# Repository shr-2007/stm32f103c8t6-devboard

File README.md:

# Canal Star Tech - STM32F103C8T6 Development Board

A custom STM32F103C8T6 development-board design created in KiCad as a hands-on electronics and PCB-design learning project.

> **Project status:** Designed in KiCad; not yet fabricated or hardware-tested.
> This repository documents the hardware design and its manufacturing outputs. It does not currently include firmware.

## Overview

The board is built around the **STM32F103C8T6** microcontroller and is intended as a compact platform for learning STM32 development, embedded hardware, and PCB design.

### Intended board features

- STM32F103C8T6 microcontroller
- 16 MHz external high-speed crystal (verify against the final schematic before fabrication)
- USB connectivity
- SWD programming/debug header
- UART header
- I²C header
- 3.3 V regulation using an AMS1117-3.3 regulator
- BOOT0 and reset access
- Front- and back-copper routing on a two-layer PCB
- GND copper zone on the back copper layer

**Important:** Confirm all component values, connector pinouts, USB circuitry, power-input limits, and regulator requirements against the committed schematic and datasheets. The feature list above reflects the current design notes and should be updated if the final schematic differs.

## Repository layout

```text
.
├── Hardware/
│   ├── KiCad/          # Native KiCad project files and required local libraries
│   ├── Gerber/         # Gerber artwork, drill files, and job file
│   └── PDF/            # Schematic PDF and other exported drawings
├── Images/             # PCB renders, layout screenshots, schematic preview
├── Documentation/
│   ├── BOM.csv         # Bill of materials template
│   └── Design_Notes.md # Design decisions and verification notes
├── LICENSE
├── README.md
└── .gitignore
```

## Design files

| Artifact | Location |
|---|---|
| KiCad schematic | `Hardware/KiCad/` |
| KiCad PCB layout | `Hardware/KiCad/` |
| Schematic PDF | `Hardware/PDF/` |
| Gerber files | `Hardware/Gerber/` |
| Excellon drill files (`.drl`) | `Hardware/Gerber/` |
| 3D render and board images | `Images/` |
| Bill of materials | `Documentation/BOM.csv` |

## Interfaces

The design currently provides headers or connections intended for:

| Interface | Purpose |
|---|---|
| USB | USB connectivity |
| SWD | Programming and debugging |
| UART | Serial communication |
| I²C | External peripherals and sensors |
| BOOT0 | Boot-mode selection |
| NRST | Reset |

Refer to the schematic and PCB silkscreen for the exact pin assignments. Do not infer pinouts from connector position alone.

## Design and verification notes

The board has been laid out as a two-layer PCB. The back copper layer contains a GND copper zone. Ground-net highlighting was used during design review to check the intended ground network.

Gerber and drill outputs were generated and opened in KiCad Gerber Viewer for visual inspection.

Before fabrication, perform and record a final review of:

- Schematic-to-PCB consistency (Update PCB from Schematic / comparison)
- Final DRC results, including any intentional exceptions
- Unconnected items
- USB schematic and routing against the STM32F103C8T6 datasheet and USB design guidance
- Crystal placement, load capacitors, and oscillator routing
- BOOT0 and NRST circuitry
- SWD header pinout
- Regulator input/output capacitors, dissipation, and input-voltage limits
- Drill sizes, plated/non-plated hole assignments, and mounting-hole dimensions
- Solder-mask and silkscreen clearances
- Manufacturer capability limits for trace width, spacing, annular ring, and drill size

A clean DRC report is useful, but it does not prove that the circuit is electrically correct or that the board has been hardware-tested.

## Getting started

1. Install KiCad (use a version compatible with the project files).
2. Clone this repository:
   ```bash
   git clone https://github.com/shr-2007/stm32f103c8t6-devboard.git
   cd stm32f103c8t6-devboard
   ```
3. Open the `.kicad_pro` file from `Hardware/KiCad/` in KiCad.
4. Check that any project-specific symbol and footprint libraries resolve correctly.
5. Review the schematic and PCB before making changes.

## Manufacturing outputs

The `Hardware/Gerber/` folder is intended to contain:

- Front and back copper Gerbers
- Front and back solder-mask Gerbers
- Front and back silkscreen Gerbers, if used
- Board outline (`Edge.Cuts`)
- PTH and NPTH Excellon drill files
- Gerber job file

Before sending files to a manufacturer, compress only the required fabrication outputs into a separate ZIP and inspect that ZIP with the manufacturer's Gerber viewer or upload preview. Do not include the native KiCad files in the fabrication ZIP unless the manufacturer specifically requests them.

## License

The hardware design is intended to be released under **CERN Open Hardware Licence Version 2 — Strongly Reciprocal (CERN-OHL-S-2.0)**. See [`LICENSE`](LICENSE).

If you add software, firmware, documentation, images, or third-party assets later, review whether separate licenses or attribution notices are appropriate. Do not assume the hardware license automatically covers third-party assets.

## Credits

Designed as an independent electronics and PCB-design
learning project.

Board branding: Canal Star Tech (fictional project identity).
Designed by: shr-2007.

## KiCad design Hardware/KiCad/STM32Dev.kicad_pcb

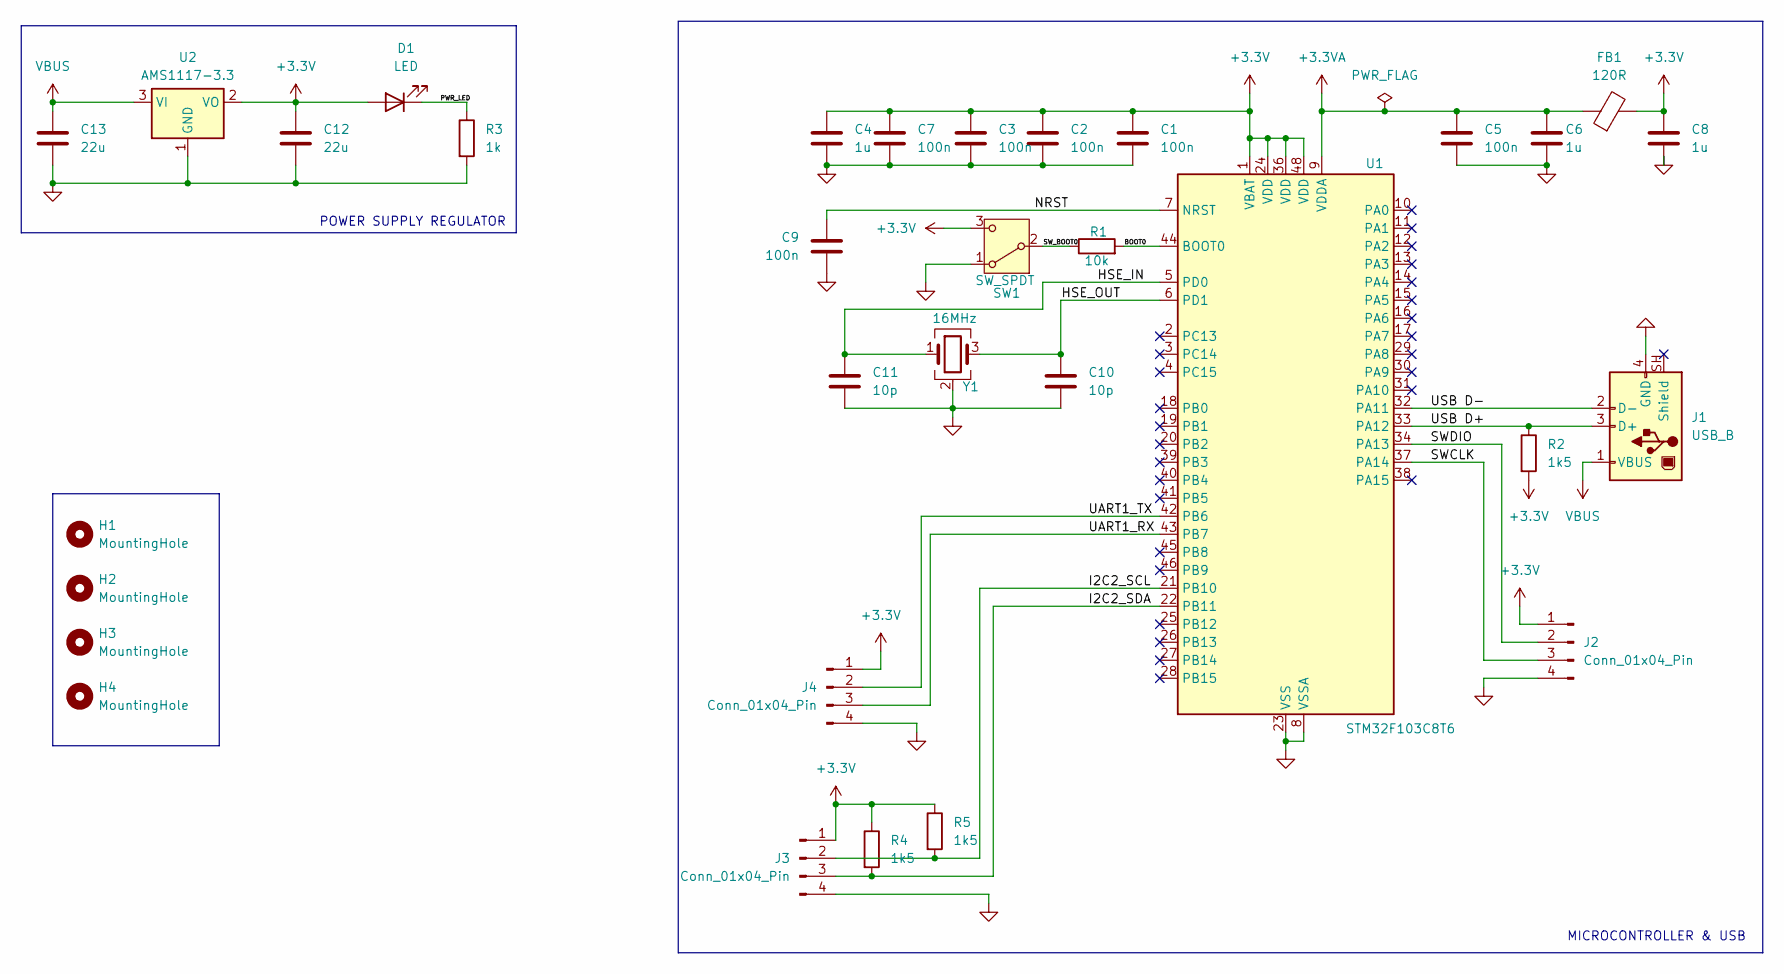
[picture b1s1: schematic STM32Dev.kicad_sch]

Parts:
C1, C2, C3, C5, C7, C9: 100n; C_0402_1005Metric_Pad0.74x0.62mm_HandSolder
C4, C6, C8: 1u; C_0603_1608Metric
C10, C11: 10p; C_0603_1608Metric
C12, C13: 22u; C_0805_2012Metric
D1: LED; LED_0603_1608Metric
FB1: 120R; R_0805_2012Metric
H1, H2, H3, H4: MountingHole; MountingHole_2.2mm_M2
J1: USB_B; USB_Micro-B_Wuerth_629105150521
J2, J3, J4: Conn_01x04_Pin; PinHeader_1x04_P2.54mm_Vertical
R1: 10k; R_0402_1005Metric
R2, R4, R5: 1k5; R_0402_1005Metric
R3: 1k; R_0402_1005Metric
SW1: SW_SPDT; SW_SPDT_PCM12
U1: STM32F103C8T6; LQFP-48_7x7mm_P0.5mm
U2: AMS1117-3.3; SOT-223-3_TabPin2
Y1: 16MHz; Crystal_SMD_3225-4Pin_3.2x2.5mm

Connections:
+3.3V: C1.1, C2.1, C3.1, C4.1, C7.1, C8.1, C12.1, D1.2 (A), FB1.2, J2.1, J3.1, J4.1, R2.2, R4.1, R5.1, SW1.3 (C), U1.1 (VBAT), U1.24 (VDD), U1.36 (VDD), U1.48 (VDD), U2.2 (VO)
+3.3VA: C5.1, C6.1, FB1.1, U1.9 (VDDA)
/BOOT0: R1.2, U1.44 (BOOT0)
/HSE_IN: C11.1, U1.5 (PD0), Y1.1
/HSE_OUT: C10.1, U1.6 (PD1), Y1.3
/I2C2_SCL: J3.2, R5.2, U1.21 (PB10)
/I2C2_SDA: J3.3, R4.2, U1.22 (PB11)
/NRST: C9.1, U1.7 (NRST)
/PWR_LED: D1.1 (K), R3.1
/SWCLK: J2.3, U1.37 (PA14)
/SWDIO: J2.2, U1.34 (PA13)
/SW_BOOT0: R1.1, SW1.2 (B)
/UART1_RX: J4.3, U1.43 (PB7)
/UART1_TX: J4.2, U1.42 (PB6)
/USB D+: J1.3 (D+), R2.1, U1.33 (PA12)
/USB D-: J1.2 (D-), U1.32 (PA11)
GND: C1.2, C2.2, C3.2, C4.2, C5.2, C6.2, C7.2, C8.2, C9.2, C10.2, C11.2, C12.2, C13.2, J1.4 (GND), J2.4, J3.4, J4.4, R3.2, SW1.1 (A), U1.8 (VSSA), U1.23 (VSS), U1.35 (VSS), U1.47 (VSS), U2.1 (GND), Y1.2 (G), Y1.4 (G)
VBUS: C13.1, J1.1 (VBUS), U2.3 (VI)

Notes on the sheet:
MICROCONTROLLER & USB
POWER SUPPLY REGULATOR

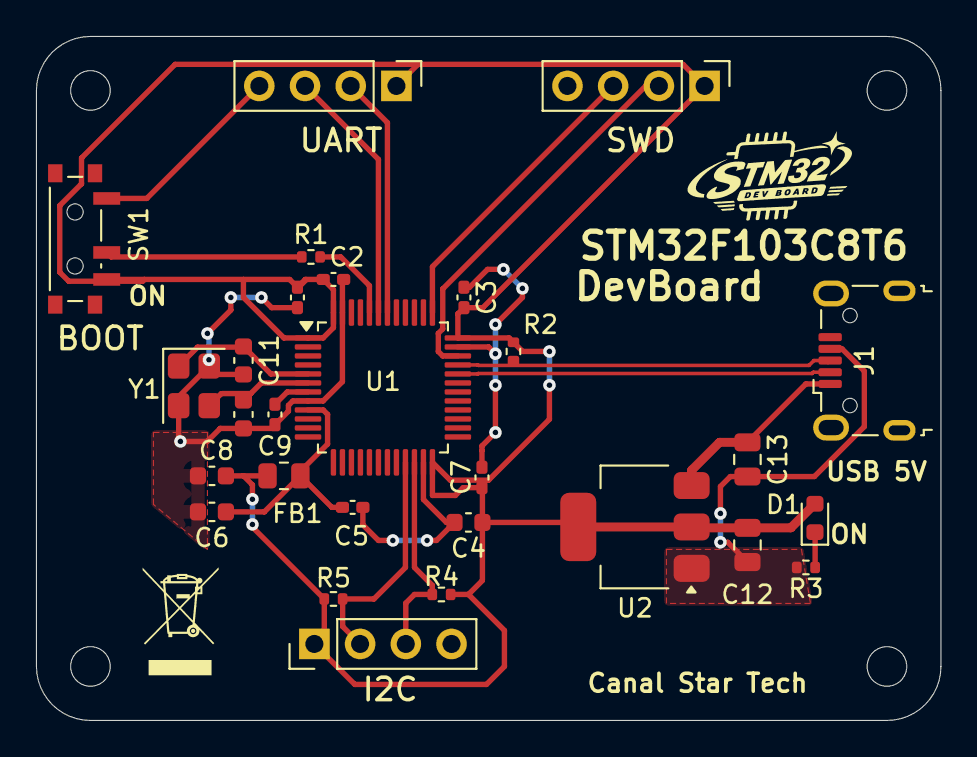
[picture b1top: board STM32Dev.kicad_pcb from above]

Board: 2 copper layers, 50.2 x 38.0 mm, 32 parts (0 on the bottom side), 18 nets.

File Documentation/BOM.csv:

"Reference","Qty","Value","DNP","Exclude from BOM","Exclude from Board","Exclude from Simulation","Exclude from Position Files","Footprint","Datasheet"
"C1,C2,C3,C5,C7,C9","6","100n","","","","","${EXCLUDE_FROM_POS_FILES}","Capacitor_SMD:C_0402_1005Metric_Pad0.74x0.62mm_HandSolder",""
"C4,C6,C8","3","1u","","","","","${EXCLUDE_FROM_POS_FILES}","Capacitor_SMD:C_0603_1608Metric",""
"C10,C11","2","10p","","","","","${EXCLUDE_FROM_POS_FILES}","Capacitor_SMD:C_0603_1608Metric",""
"C12,C13","2","22u","","","","","${EXCLUDE_FROM_POS_FILES}","Capacitor_SMD:C_0805_2012Metric",""
"D1","1","LED","","","","","${EXCLUDE_FROM_POS_FILES}","LED_SMD:LED_0603_1608Metric",""
"FB1","1","120R","","","","","${EXCLUDE_FROM_POS_FILES}","Resistor_SMD:R_0805_2012Metric",""
"J1","1","USB_B","","","","","${EXCLUDE_FROM_POS_FILES}","Connector_USB:USB_Micro-B_Wuerth_629105150521",""
"J2,J3,J4","3","Conn_01x04_Pin","","","","","${EXCLUDE_FROM_POS_FILES}","Connector_PinHeader_2.54mm:PinHeader_1x04_P2.54mm_Vertical",""
"R1","1","10k","","","","","${EXCLUDE_FROM_POS_FILES}","Resistor_SMD:R_0402_1005Metric",""
"R2,R4,R5","3","1k5","","","","","${EXCLUDE_FROM_POS_FILES}","Resistor_SMD:R_0402_1005Metric",""
"R3","1","1k","","","","","${EXCLUDE_FROM_POS_FILES}","Resistor_SMD:R_0402_1005Metric",""
"SW1","1","SW_SPDT","","","","","${EXCLUDE_FROM_POS_FILES}","Button_Switch_SMD:SW_SPDT_PCM12",""
"U1","1","STM32F103C8T6","","","","","${EXCLUDE_FROM_POS_FILES}","Package_QFP:LQFP-48_7x7mm_P0.5mm","https://www.st.com/resource/en/datasheet/stm32f103c8.pdf"
"U2","1","AMS1117-3.3","","","","","${EXCLUDE_FROM_POS_FILES}","Package_TO_SOT_SMD:SOT-223-3_TabPin2","http://www.advanced-monolithic.com/pdf/ds1117.pdf"
"Y1","1","16MHz","","","","","${EXCLUDE_FROM_POS_FILES}","Crystal:Crystal_SMD_3225-4Pin_3.2x2.5mm",""
